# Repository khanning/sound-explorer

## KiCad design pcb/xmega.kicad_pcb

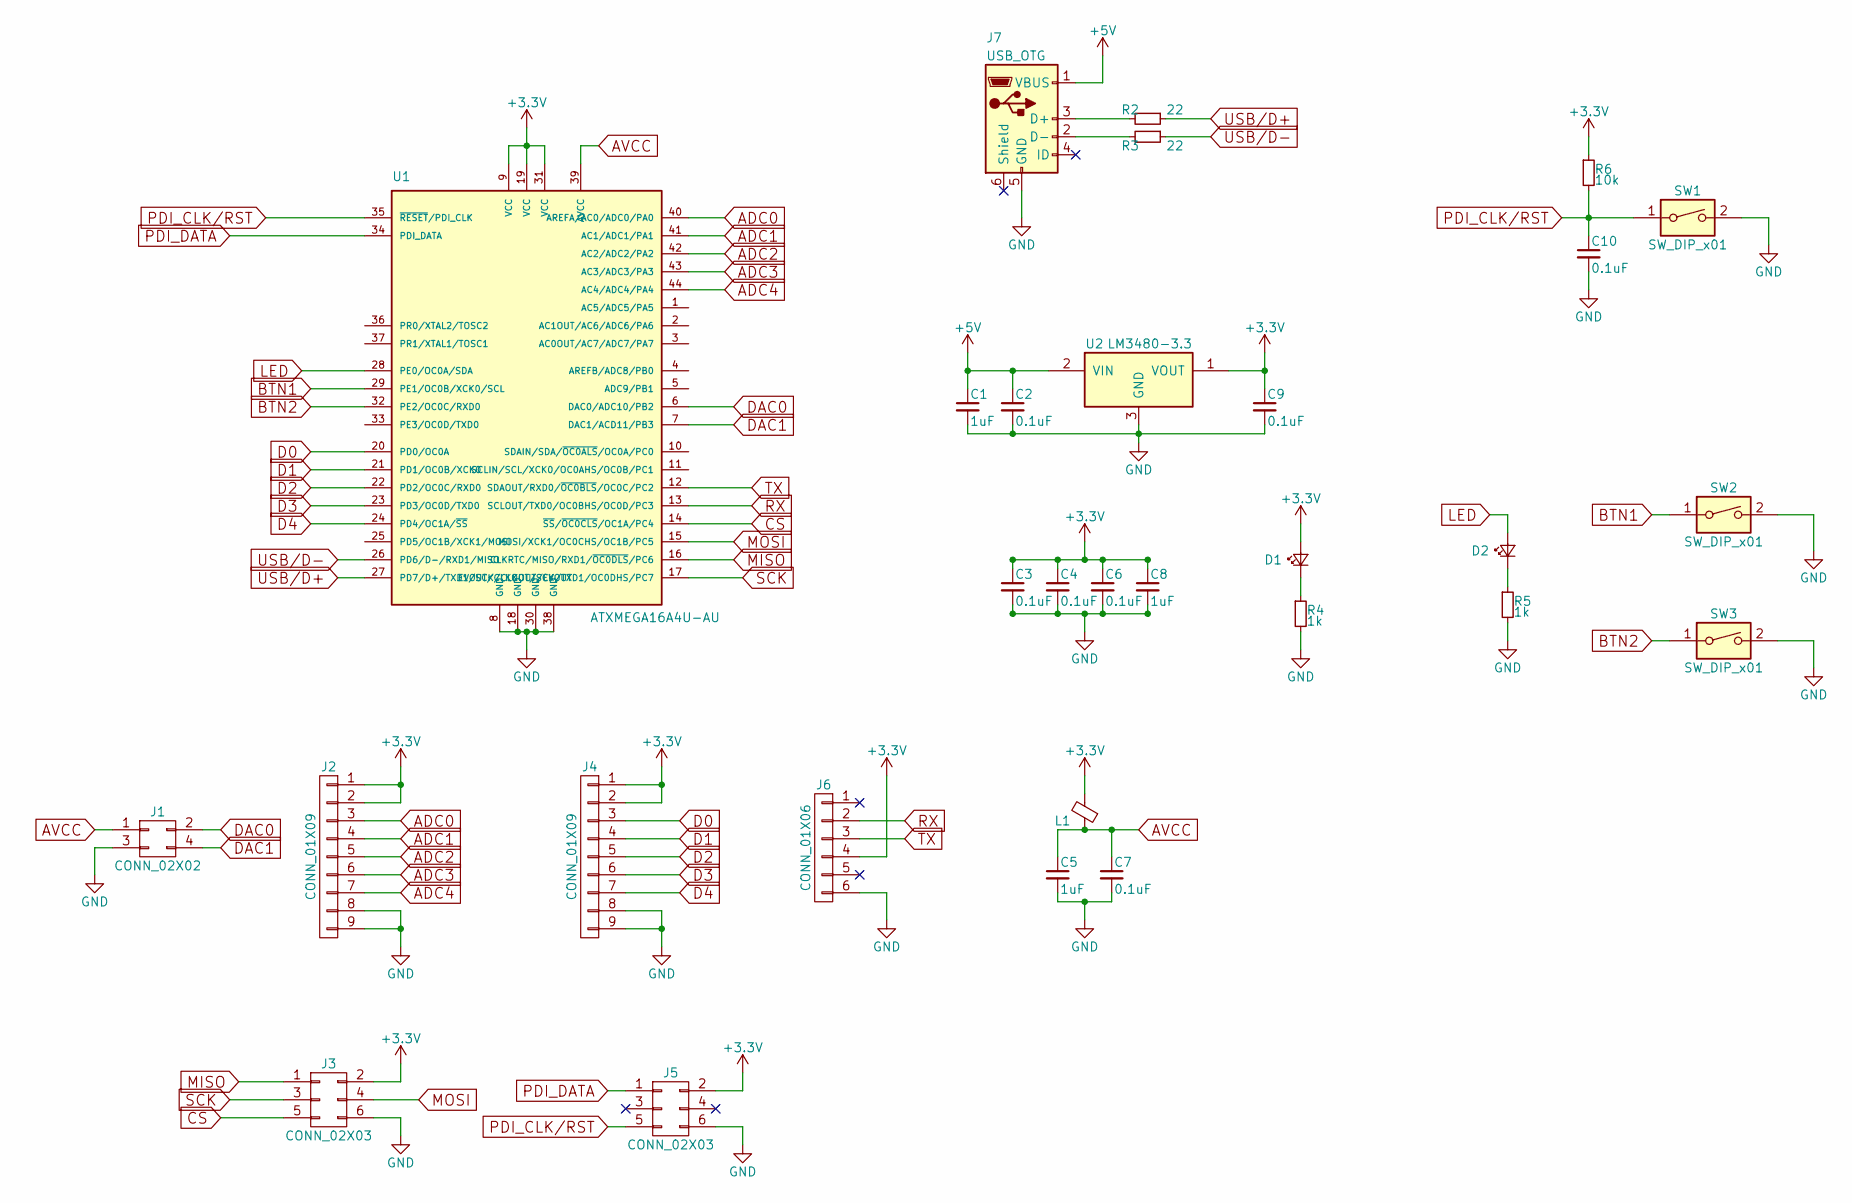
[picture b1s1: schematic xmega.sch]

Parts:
C1, C5, C8: 1uF; C_1206
C2, C3, C4, C6, C7, C9, C10: 0.1uF; C_1206
D1, D2: green; LED_1206
J1: CONN_02X02; Pin_Header_Straight_2x02_Pitch2.54mm_SMD
J2, J4: CONN_01X09; Pin_Header_Straight_1x09_Pitch2.54mm_SMD_Pin1Left
J3, J5: CONN_02X03; Pin_Header_Straight_2x03_Pitch2.54mm_SMD
J6: CONN_01X06; 1x6_smd_pads
J7: USB_OTG; microUSB_SZ_hand
L1: Ferrite_Bead_Small; R_0805
R2, R3: 22; R_1206
R4, R5: 1k; R_1206
R6: 10k; R_1206
SW1, SW2, SW3: SW_DIP_x01; tl6120_switch
U1: ATXMEGA16A4U-AU; 44-TQFP
U2: LM3480-3.3; SOT-23

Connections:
+3V3: C3.1, C4.1, C6.1, C8.1, C9.1, D1.2 (A), J2.1, J2.2, J3.2, J4.1, J4.2, J5.2, J6.4, L1.2, R6.1, U1.9 (VCC), U1.19 (VCC), U1.31 (VCC), U2.1 (VOUT)
+5V: C1.1, C2.1, J7.1 (VBUS), U2.2 (VIN)
ADC0: J2.3, U1.40 (AREFA/AC0/ADC0/PA0)
ADC1: J2.4, U1.41 (AC1/ADC1/PA1)
ADC2: J2.5, U1.42 (AC2/ADC2/PA2)
ADC3: J2.6, U1.43 (AC3/ADC3/PA3)
ADC4: J2.7, U1.44 (AC4/ADC4/PA4)
AVCC: C5.1, C7.1, J1.1, L1.1, U1.39 (AVCC)
BTN1: SW2.1, U1.29 (PE1/OC0B/XCK0/SCL)
BTN2: SW3.1, U1.32 (PE2/OC0C/RXD0)
CS: J3.5, U1.14 (~SS~/~OC0CLS~/OC1A/PC4)
D0: J4.3, U1.20 (PD0/OC0A)
D1: J4.4, U1.21 (PD1/OC0B/XCK0)
D2: J4.5, U1.22 (PD2/OC0C/RXD0)
D3: J4.6, U1.23 (PD3/OC0D/TXD0)
D4: J4.7, U1.24 (PD4/OC1A/~SS~)
DAC0: J1.2, U1.6 (DAC0/ADC10/PB2)
DAC1: J1.4, U1.7 (DAC1/ACD11/PB3)
GND: C1.2, C2.2, C3.2, C4.2, C5.2, C6.2, C7.2, C8.2, C9.2, C10.2, J1.3, J2.8, J2.9, J3.6, J4.8, J4.9, J5.6, J6.6, J7.5 (GND), R4.2, R5.2, SW1.2, SW2.2, SW3.2, U1.8 (GND), U1.18 (GND), U1.30 (GND), U1.38 (GND), U2.3 (GND)
LED: D2.2 (A), U1.28 (PE0/OC0A/SDA)
MISO: J3.1, U1.16 (CLKRTC/MISO/RXD1/~OC0DLS~/PC6)
MOSI: J3.4, U1.15 (MOSI/XCK1/OC0CHS/OC1B/PC5)
unnamed: D1.1 (K), R4.1
unnamed: D2.1 (K), R5.1
unnamed: J7.2 (D-), R3.2
unnamed: J7.3 (D+), R2.2
PDI_CLK/RST: C10.1, J5.5, R6.2, SW1.1, U1.35 (~RESET~/PDI_CLK)
PDI_DATA: J5.1, U1.34 (PDI_DATA)
RX: J6.2, U1.13 (SCLOUT/TXD0/OC0BHS/OC0D/PC3)
SCK: J3.3, U1.17 (EVOUT/CLKOUT/SCK/TXD1/OC0DHS/PC7)
TX: J6.3, U1.12 (SDAOUT/RXD0/~OC0BLS~/OC0C/PC2)
USB/D+: R2.1, U1.27 (PD7/D+/TXD1/SCK/CLKOUT/EVOUT)
USB/D-: R3.1, U1.26 (PD6/D-/RXD1/MISO)

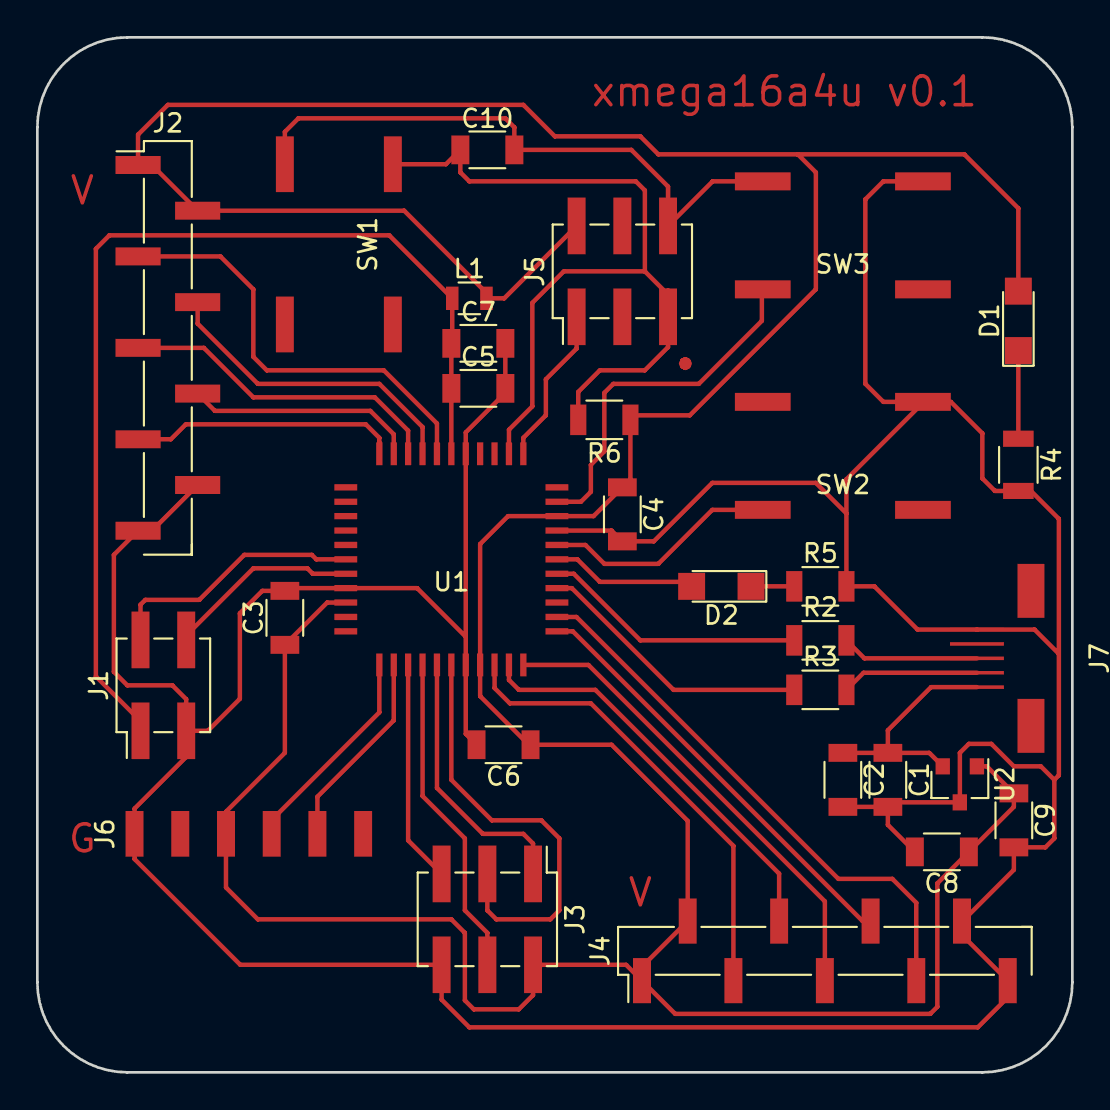
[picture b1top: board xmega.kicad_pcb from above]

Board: 2 copper layers, 57.5 x 57.5 mm, 30 parts (0 on the bottom side), 33 nets.

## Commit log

2018-01-10 Removed compiled files
2018-01-11 Added SD breakout board
2018-01-19 Added FATfs for SD card communication. Implementation still buggy.
2018-01-19 Added TODO list
2018-01-20 Added timer interrupt to drive SD communication
2018-01-22 Create serial lib and lib directory
